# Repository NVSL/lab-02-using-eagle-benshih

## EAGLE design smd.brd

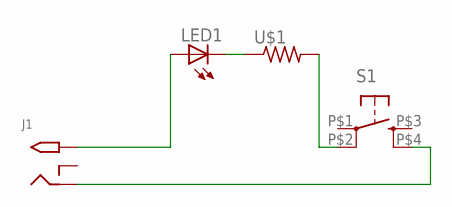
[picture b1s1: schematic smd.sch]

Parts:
J1: 2.1MMJACKTHM; PJ-102A
LED1: LED5MM
S1: BUTTON-TACTILE-SMD; BUTTON-TACTILE-SQUARE_SMD
U$1: RESISTORTH-1/4W-CARBON; RESAD1160W55L680D260_HS

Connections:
unnamed: LED1.K (C), U$1.1
unnamed: S1.P$2 (P1), U$1.2
unnamed: J1.TIP, LED1.A
unnamed: J1.RING, S1.P$4 (S1)

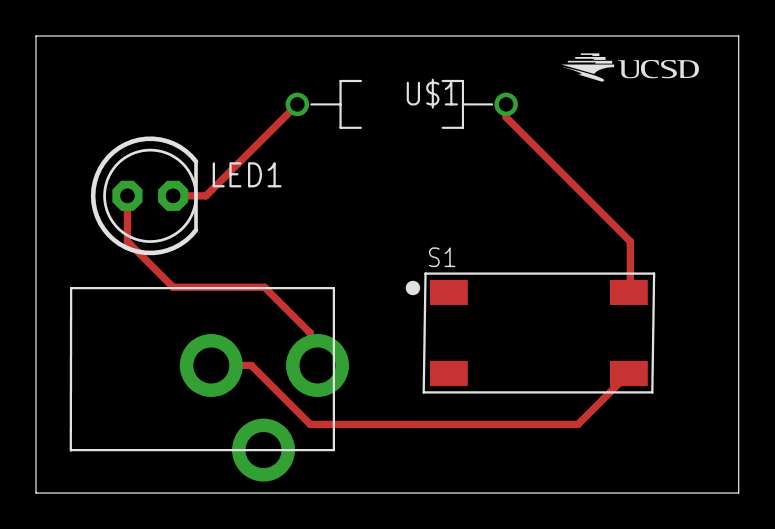
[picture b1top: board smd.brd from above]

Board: 2 copper layers, 39.0 x 25.4 mm, 5 parts (0 on the bottom side), 4 nets.

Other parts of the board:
U$2: UCSD_LOGO

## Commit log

2016-04-19 Schematic, board, and CAM files for flashlight PCB.
2016-04-22 Renamed throughhole files to throughole.*. Added freeDFM results.
2016-04-22 Removed files that were originally flashlight.*
2016-04-22 Updated eagle library for SMD tactile button.
2016-04-22 smd sch, brd, and CAM files.
2016-04-22 Updated Eagle parts library.
2016-04-22 smd freeDFM results.
